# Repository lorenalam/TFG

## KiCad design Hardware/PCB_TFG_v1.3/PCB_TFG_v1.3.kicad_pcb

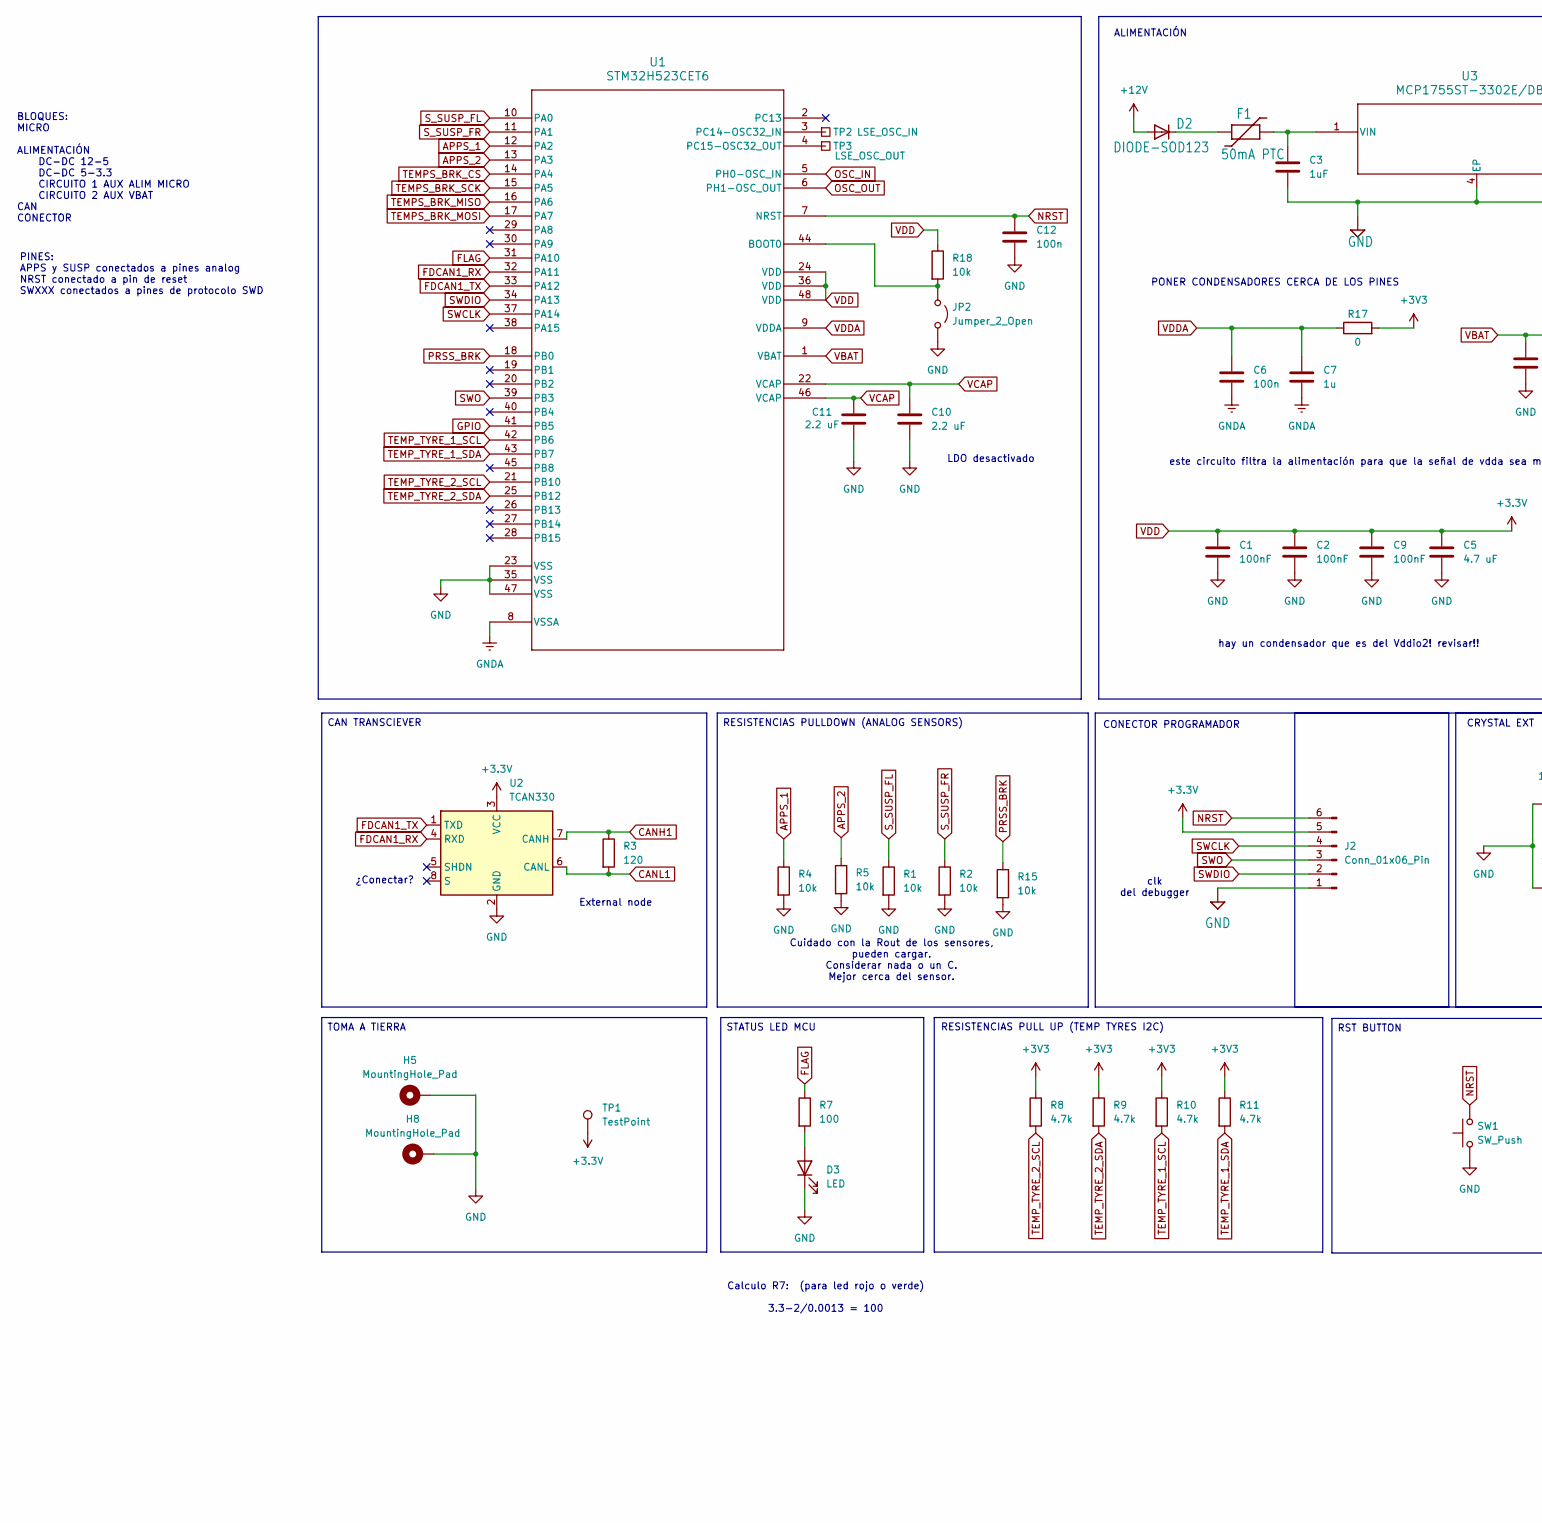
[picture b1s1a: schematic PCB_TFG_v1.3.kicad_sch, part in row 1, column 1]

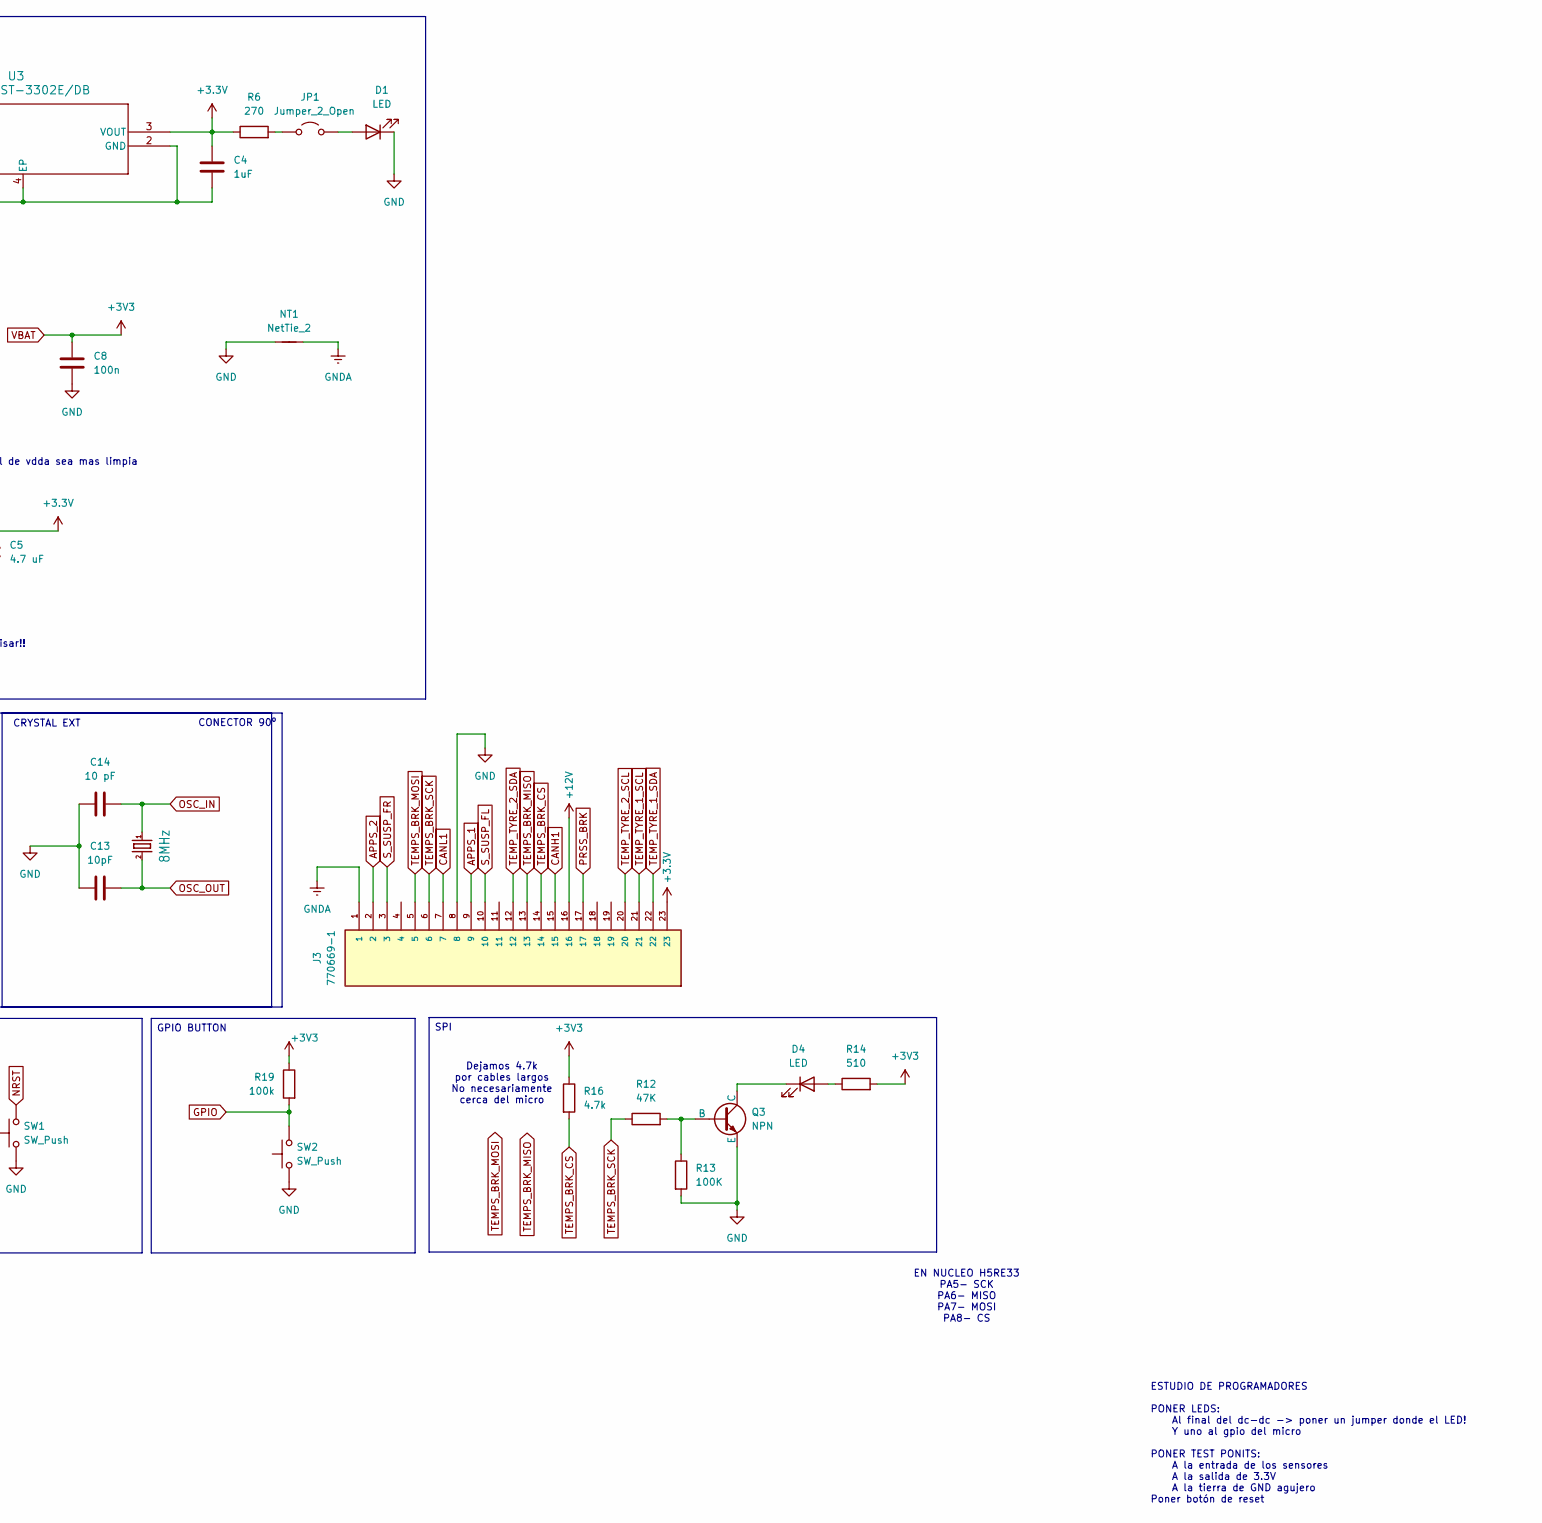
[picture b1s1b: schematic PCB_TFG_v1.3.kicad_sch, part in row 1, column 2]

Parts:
C1, C2, C9: 100nF; C_0805_2012Metric_Pad1.18x1.45mm_HandSolder
C3, C4: 1uF; C_0805_2012Metric_Pad1.18x1.45mm_HandSolder
C5: 4.7 uF; C_0805_2012Metric_Pad1.18x1.45mm_HandSolder
C6, C8, C12: 100n; C_0805_2012Metric_Pad1.18x1.45mm_HandSolder
C7: 1u; C_0805_2012Metric_Pad1.18x1.45mm_HandSolder
C10, C11: 2.2 uF; C_0805_2012Metric_Pad1.18x1.45mm_HandSolder
C13: 10pF; C_0805_2012Metric_Pad1.18x1.45mm_HandSolder
C14: 10 pF; C_0805_2012Metric_Pad1.18x1.45mm_HandSolder
D1, D3, D4: LED; LED_0805_2012Metric_Pad1.15x1.40mm_HandSolder
D2: DIODE-SOD123; SOD123
F1: 50mA PTC; 1206
H5, H8: MountingHole_Pad; MountingHole_3.2mm_M3_ISO14580_Pad_TopBottom
J2: Conn_01x06_Pin; PinHeader_2x03_P2.54mm_Vertical
J3: 770669-1; TE_770669-1; PARTREV K11
JP1: Jumper_2_Open; SolderJumper-2_P1.3mm_Open_RoundedPad1.0x1.5mm
JP2: Jumper_2_Open; PinHeader_1x02_P2.54mm_Vertical
NT1: NetTie_2; NetTie-2_SMD_Pad0.5mm
Q1: 8MHz; CTS406
Q3: NPN; TSOT-23
R1, R2, R4, R5, R15, R18: 10k; R_0805_2012Metric_Pad1.20x1.40mm_HandSolder
R3: 120; R_0805_2012Metric_Pad1.20x1.40mm_HandSolder
R6: 270; R_0805_2012Metric_Pad1.20x1.40mm_HandSolder
R7: 100; R_0805_2012Metric_Pad1.20x1.40mm_HandSolder
R8, R9, R10, R11, R16: 4.7k; R_0805_2012Metric_Pad1.20x1.40mm_HandSolder
R12: 47K; R_0805_2012Metric_Pad1.20x1.40mm_HandSolder
R13: 100K; R_0805_2012Metric_Pad1.20x1.40mm_HandSolder
R14: 510; R_0805_2012Metric_Pad1.20x1.40mm_HandSolder
R17: 0; R_0805_2012Metric_Pad1.20x1.40mm_HandSolder
R19: 100k; R_0805_2012Metric_Pad1.20x1.40mm_HandSolder
SW1, SW2: SW_Push; SW_SPST_B3U-1000P-B
TP1: TestPoint; Pin_D1.0mm_L10.0mm
TP2: LSE_OSC_IN; TestPoint_Pad_1.0x1.0mm
TP3: LSE_OSC_OUT; TestPoint_Pad_1.0x1.0mm
U1: STM32H523CET6; LQFP48_STM
U2: TCAN330; SOIC-8_3.9x4.9mm_P1.27mm
U3: MCP1755ST-3302E/DB; SOT-223_3MC_MCH

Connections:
+12V: D2.A, J3.16
APPS_1: J3.9, R4.1, U1.12 (PA2)
APPS_2: J3.2, R5.1, U1.13 (PA3)
CANH1: J3.15, R3.1, U2.7 (CANH)
CANL1: J3.7, R3.2, U2.6 (CANL)
FDCAN1_RX: U1.32 (PA11), U2.4 (RXD)
FDCAN1_TX: U1.33 (PA12), U2.1 (TXD)
FLAG: R7.1, U1.31 (PA10)
GND: C1.2, C2.2, C3.2, C4.2, C5.2, C8.1, C9.2, C10.2, C11.2, C12.1, C13.1, C14.1, D1.1 (K), D3.1 (K), H5.1 (1_1), H8.1 (1_1), J2.1, J3.8, JP2.2 (B), NT1.1, Q3.3 (E), R1.2, R2.2, R4.2, R5.2, R13.2, R15.2, SW1.1, SW2.1, U1.23 (VSS), U1.35 (VSS), U1.47 (VSS), U2.2 (GND), U3.2 (GND), U3.4 (EP)
GNDA: C6.1, C7.1, J3.1, NT1.2, U1.8 (VSSA)
GPIO: R19.2, SW2.2, U1.41 (PB5)
NRST: C12.2, J2.6, SW1.2, U1.7 (NRST)
unnamed: D1.2 (A), JP1.2 (B)
unnamed: D2.C, F1.P$1
unnamed: D3.2 (A), R7.2
unnamed: D4.2 (A), R14.1
unnamed: D4.1 (K), Q3.1 (C)
unnamed: JP1.1 (A), R6.2
unnamed: JP2.1 (A), R18.2, U1.44 (BOOT0)
unnamed: Q3.2 (B), R12.2, R13.1
unnamed: TP2.1 (1_1), U1.3 (PC14-OSC32_IN)
unnamed: TP3.1 (1_1), U1.4 (PC15-OSC32_OUT)
unnamed: C3.1, F1.P$2, U3.1 (VIN)
OSC_IN: C14.2, Q1.1, U1.5 (PH0-OSC_IN)
OSC_OUT: C13.2, Q1.3 (2), U1.6 (PH1-OSC_OUT)
PRSS_BRK: J3.17, R15.1, U1.18 (PB0)
SWCLK: J2.4, U1.37 (PA14)
SWDIO: J2.2, U1.34 (PA13)
SWO: J2.3, U1.39 (PB3)
S_SUSP_FL: J3.10, R1.1, U1.10 (PA0)
S_SUSP_FR: J3.3, R2.1, U1.11 (PA1)
TEMPS_BRK_CS: J3.14, R16.2, U1.14 (PA4)
TEMPS_BRK_MISO: J3.13, U1.16 (PA6)
TEMPS_BRK_MOSI: J3.5, U1.17 (PA7)
TEMPS_BRK_SCK: J3.6, R12.1, U1.15 (PA5)
TEMP_TYRE_1_SCL: J3.21, R10.2, U1.42 (PB6)
TEMP_TYRE_1_SDA: J3.22, R11.2, U1.43 (PB7)
TEMP_TYRE_2_SCL: J3.20, R8.2, U1.21 (PB10)
TEMP_TYRE_2_SDA: J3.12, R9.2, U1.25 (PB12)
VBAT: C8.2, R8.1, R9.1, R10.1, R11.1, R14.2, R16.1, R17.2, R19.1, U1.1 (VBAT)
VCAP: C10.1, C11.1, U1.22 (VCAP), U1.46 (VCAP)
VDD: C1.1, C2.1, C4.1, C5.1, C9.1, J2.5, J3.23, R6.1, R18.1, TP1.1 (1_1), U1.24 (VDD), U1.36 (VDD), U1.48 (VDD), U2.3 (VCC), U3.3 (VOUT)
VDDA: C6.2, C7.2, R17.1, U1.9 (VDDA)

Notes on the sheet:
PONER CONDENSADORES CERCA DE LOS PINES
ESTUDIO DE PROGRAMADORES PONER LEDS: Al final del dc-dc -> poner un jumper donde el LED! Y uno al gpio del micro PONER TEST PONITS: A la entrada de los sensores A la salida de 3.3V A la tierra de GND agujero Poner botón de reset
EN NUCLEO H5RE33 PA5- SCK PA6- MISO PA7- MOSI PA8- CS
BLOQUES: MICRO ALIMENTACIÓN DC-DC 12-5 DC-DC 5-3.3 CIRCUITO 1 AUX ALIM MICRO CIRCUITO 2 AUX VBAT CAN CONECTOR
CONECTOR PROGRAMADOR
clk del debugger
Cuidado con la Rout de los sensores, pueden cargar. Considerar nada o un C. Mejor cerca del sensor.
RESISTENCIAS PULL UP (TEMP TYRES I2C)
Calculo R7: (para led rojo o verde) 3.3-2/0.0013 = 100
Dejamos 4.7k por cables largos No necesariamente cerca del micro
External node
LDO desactivado
este circuito filtra la alimentación para que la señal de vdda sea mas limpia
¿Conectar?
PINES: APPS y SUSP conectados a pines analog NRST conectado a pin de reset SWXXX conectados a pines de protocolo SWD
hay un condensador que es del Vddio2! revisar!!
ALIMENTACIÓN
CRYSTAL EXT
TOMA A TIERRA
RESISTENCIAS PULLDOWN (ANALOG SENSORS)
GPIO BUTTON
CONECTOR 90º
SPI
CAN TRANSCIEVER
STATUS LED MCU
RST BUTTON

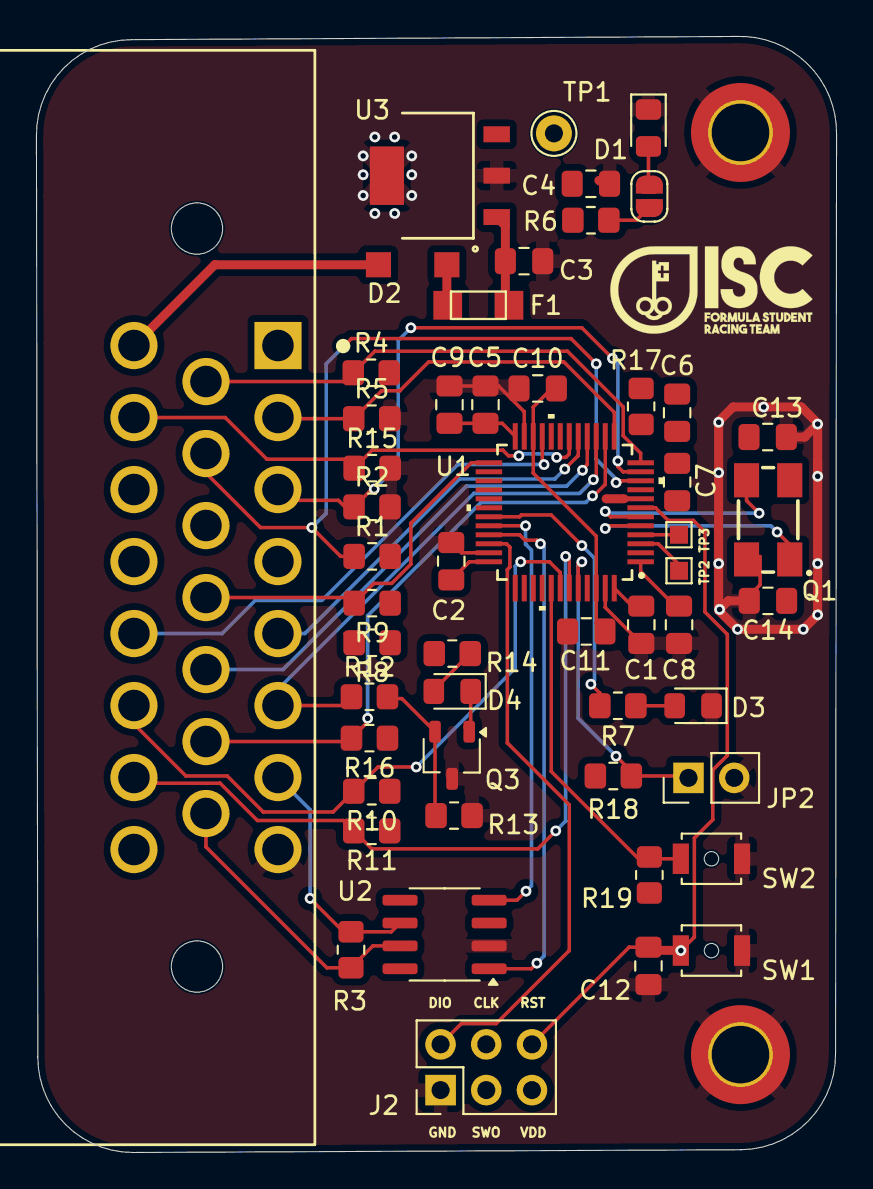
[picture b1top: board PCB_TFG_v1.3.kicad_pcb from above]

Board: 4 copper layers, 44.4 x 62.0 mm, 55 parts (0 on the bottom side), 43 nets.

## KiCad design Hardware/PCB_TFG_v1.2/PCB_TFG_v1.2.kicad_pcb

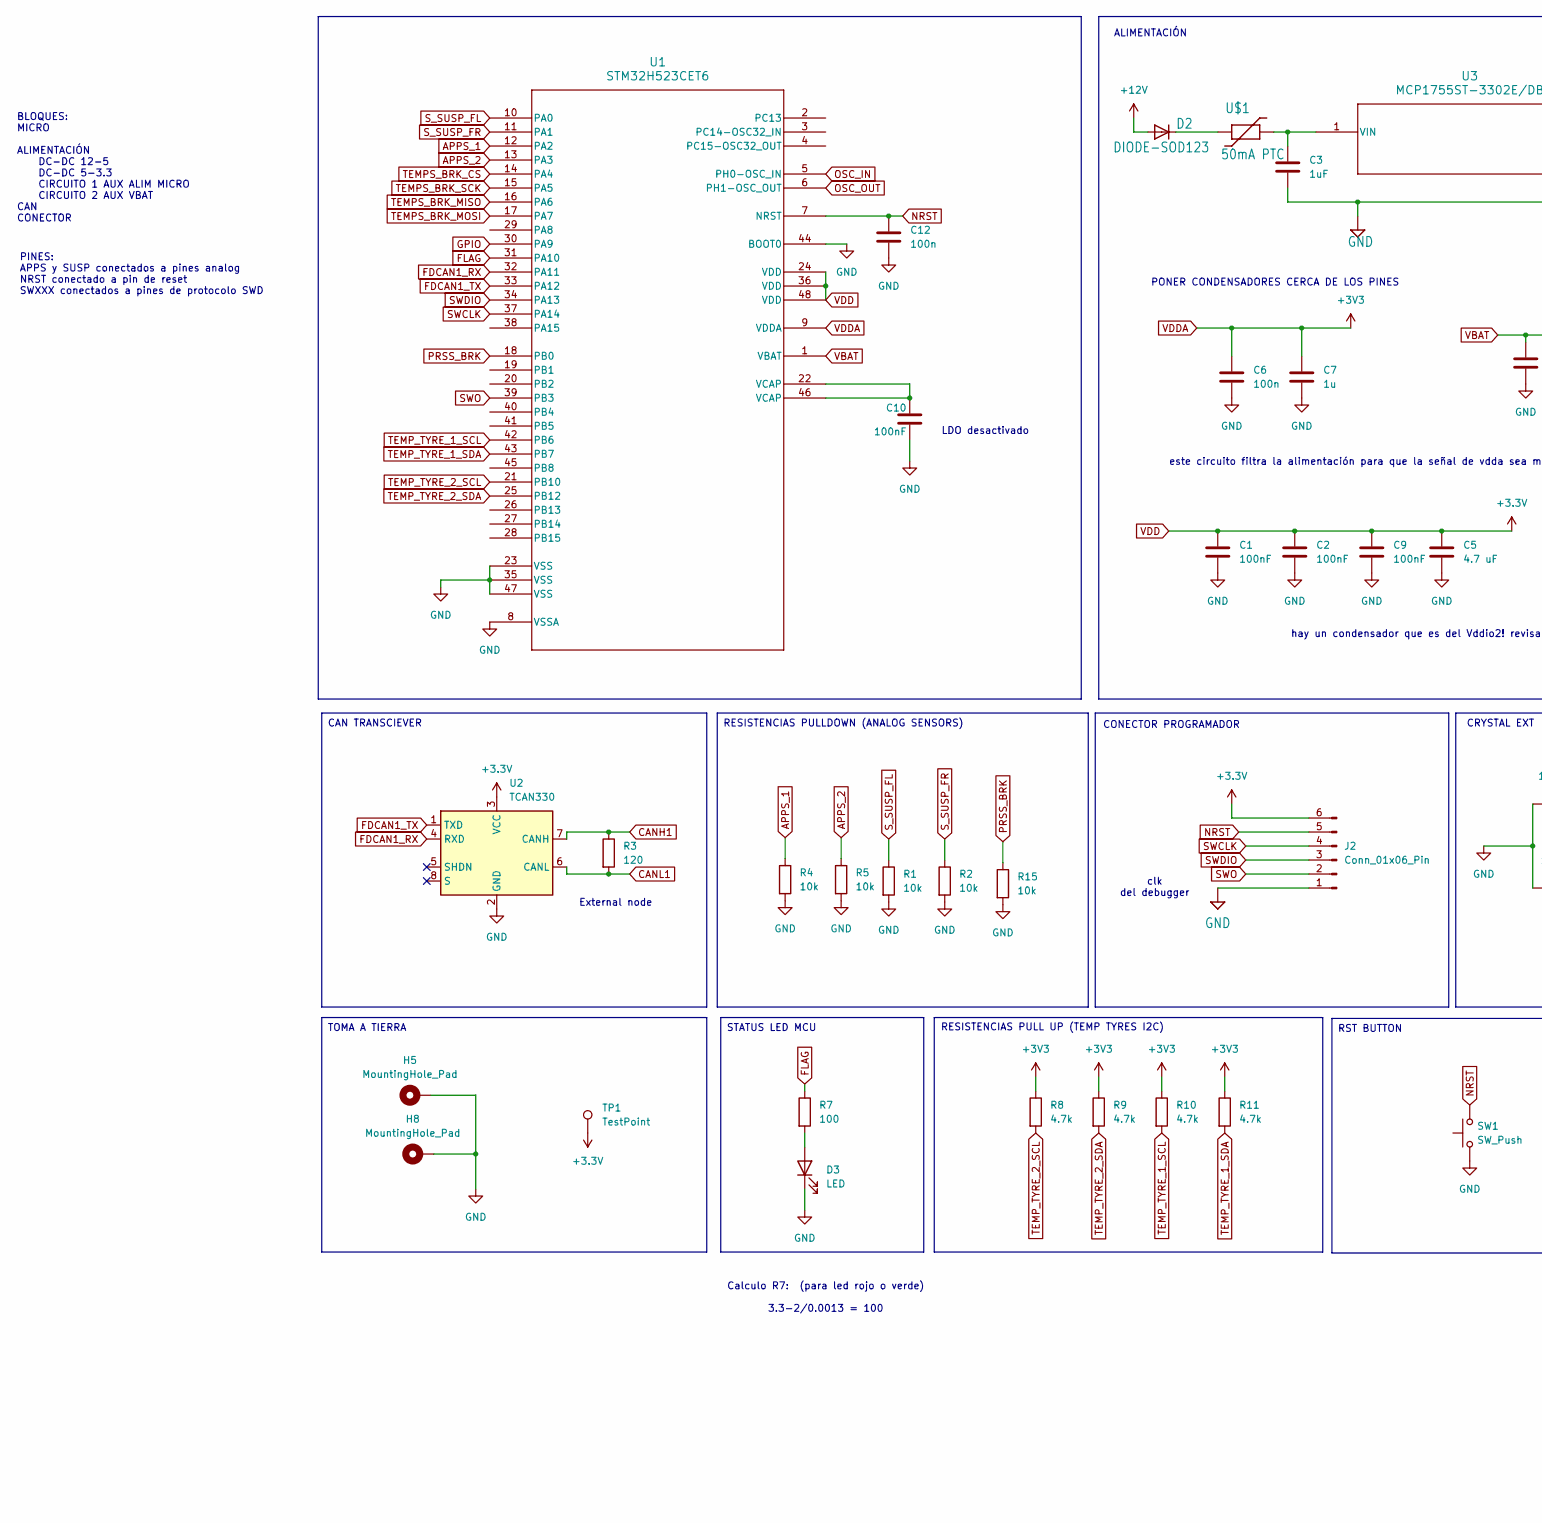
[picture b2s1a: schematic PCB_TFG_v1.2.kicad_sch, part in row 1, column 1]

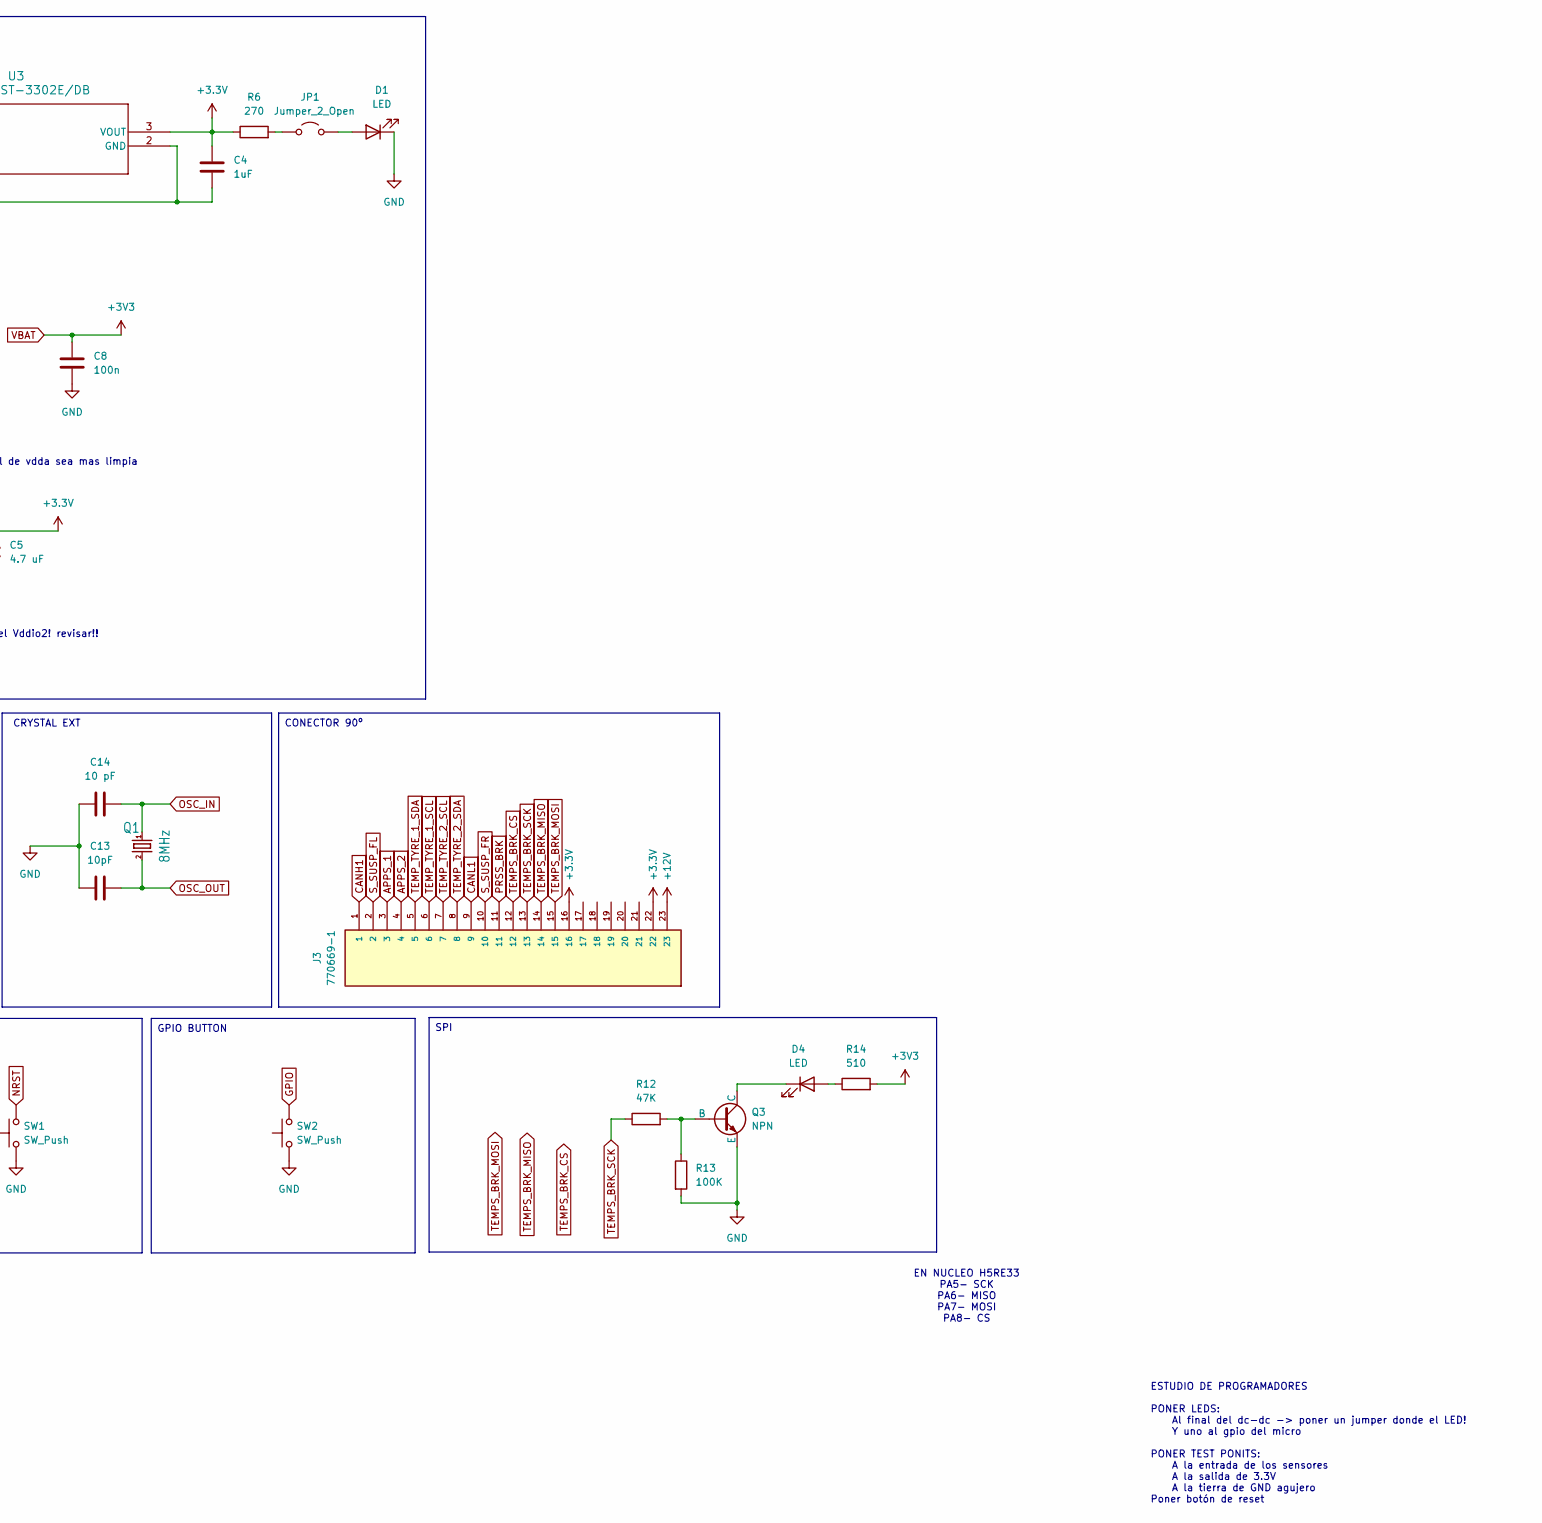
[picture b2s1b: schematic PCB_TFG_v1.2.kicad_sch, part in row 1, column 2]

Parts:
C1, C2, C9, C10: 100nF; C_0805_2012Metric_Pad1.18x1.45mm_HandSolder
C3, C4: 1uF; C_0805_2012Metric_Pad1.18x1.45mm_HandSolder
C5: 4.7 uF; C_0805_2012Metric_Pad1.18x1.45mm_HandSolder
C6, C8: 100n; C_0805_2012Metric_Pad1.18x1.45mm_HandSolder
C7: 1u; C_0805_2012Metric_Pad1.18x1.45mm_HandSolder
C12: 100n; C_0603_1608Metric_Pad1.08x0.95mm_HandSolder
C13: 10pF; C_0805_2012Metric_Pad1.18x1.45mm_HandSolder
C14: 10 pF; C_0805_2012Metric_Pad1.18x1.45mm_HandSolder
D1, D3, D4: LED; LED_0805_2012Metric_Pad1.15x1.40mm_HandSolder
D2: DIODE-SOD123; SOD123
H5, H8: MountingHole_Pad; MountingHole_3.2mm_M3_ISO14580_Pad_TopBottom
J2: Conn_01x06_Pin; PinHeader_2x03_P2.54mm_Vertical
J3: 770669-1; TE_770669-1; PARTREV K11
JP1: Jumper_2_Open; SolderJumper-2_P1.3mm_Open_RoundedPad1.0x1.5mm
Q1: 8MHz; CTS406
Q3: NPN; TSOT-23
R1, R2, R4, R5, R15: 10k; R_0805_2012Metric_Pad1.20x1.40mm_HandSolder
R3: 120; R_0805_2012Metric_Pad1.20x1.40mm_HandSolder
R6: 270; R_0805_2012Metric_Pad1.20x1.40mm_HandSolder
R7: 100; R_0805_2012Metric_Pad1.20x1.40mm_HandSolder
R8, R9, R10, R11: 4.7k; R_0805_2012Metric_Pad1.20x1.40mm_HandSolder
R12: 47K; R_0805_2012Metric_Pad1.20x1.40mm_HandSolder
R13: 100K; R_0805_2012Metric_Pad1.20x1.40mm_HandSolder
R14: 510; R_0805_2012Metric_Pad1.20x1.40mm_HandSolder
SW1, SW2: SW_Push; SW_PUSH_6mm_H4.3mm
TP1: TestPoint; Pin_D1.0mm_L10.0mm
U1: STM32H523CET6; LQFP48_STM
U2: TCAN330; SOIC-8_3.9x4.9mm_P1.27mm
U3: MCP1755ST-3302E/DB; SOT-223_3MC_MCH
U$1: 50mA PTC; 1206

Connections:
+12V: D2.A, J3.23
APPS_1: J3.3, R4.1, U1.12 (PA2)
APPS_2: J3.4, R5.1, U1.13 (PA3)
CANH1: J3.1, R3.1, U2.7 (CANH)
CANL1: J3.9, R3.2, U2.6 (CANL)
FDCAN1_RX: U1.32 (PA11), U2.4 (RXD)
FDCAN1_TX: U1.33 (PA12), U2.1 (TXD)
FLAG: R7.1, U1.31 (PA10)
GND: C1.2, C2.2, C3.2, C4.2, C5.2, C6.1, C7.1, C8.1, C9.2, C10.2, C12.1, C13.1, C14.1, D1.1 (K), D3.1 (K), H5.1, H8.1, J2.1, Q3.3 (E), R1.2, R2.2, R4.2, R5.2, R13.2, R15.2, SW1.1, SW2.1, U1.8 (VSSA), U1.23 (VSS), U1.35 (VSS), U1.44 (BOOT0), U1.47 (VSS), U2.2 (GND), U3.2 (GND)
GPIO: SW2.2, U1.30 (PA9)
NRST: C12.2, J2.5, SW1.2, U1.7 (NRST)
unnamed: C10.1, U1.22 (VCAP), U1.46 (VCAP)
unnamed: D1.2 (A), JP1.2 (B)
unnamed: D2.C, U$1.P$1
unnamed: D3.2 (A), R7.2
unnamed: D4.2 (A), R14.1
unnamed: D4.1 (K), Q3.1 (C)
unnamed: JP1.1 (A), R6.2
unnamed: Q3.2 (B), R12.2, R13.1
unnamed: C3.1, U3.1 (VIN), U$1.P$2
OSC_IN: C14.2, Q1.1, U1.5 (PH0-OSC_IN)
OSC_OUT: C13.2, Q1.3 (2), U1.6 (PH1-OSC_OUT)
PRSS_BRK: J3.11, R15.1, U1.18 (PB0)
SWCLK: J2.4, U1.37 (PA14)
SWDIO: J2.3, U1.34 (PA13)
SWO: J2.2, U1.39 (PB3)
S_SUSP_FL: J3.2, R1.1, U1.10 (PA0)
S_SUSP_FR: J3.10, R2.1, U1.11 (PA1)
TEMPS_BRK_CS: J3.12, U1.14 (PA4)
TEMPS_BRK_MISO: J3.14, U1.16 (PA6)
TEMPS_BRK_MOSI: J3.15, U1.17 (PA7)
TEMPS_BRK_SCK: J3.13, R12.1, U1.15 (PA5)
TEMP_TYRE_1_SCL: J3.6, R10.2, U1.42 (PB6)
TEMP_TYRE_1_SDA: J3.5, R11.2, U1.43 (PB7)
TEMP_TYRE_2_SCL: J3.7, R8.2, U1.21 (PB10)
TEMP_TYRE_2_SDA: J3.8, R9.2, U1.25 (PB12)
VBAT: C6.2, C7.2, C8.2, R8.1, R9.1, R10.1, R11.1, R14.2, U1.1 (VBAT), U1.9 (VDDA)
VDD: C1.1, C2.1, C4.1, C5.1, C9.1, J2.6, J3.16, J3.22, R6.1, TP1.1, U1.24 (VDD), U1.36 (VDD), U1.48 (VDD), U2.3 (VCC), U3.3 (VOUT)

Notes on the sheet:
TOMA A TIERRA
RESISTENCIAS PULLDOWN (ANALOG SENSORS)
GPIO BUTTON
CONECTOR 90º
SPI
CAN TRANSCIEVER
STATUS LED MCU
RST BUTTON
PONER CONDENSADORES CERCA DE LOS PINES
ESTUDIO DE PROGRAMADORES PONER LEDS: Al final del dc-dc -> poner un jumper donde el LED! Y uno al gpio del micro PONER TEST PONITS: A la entrada de los sensores A la salida de 3.3V A la tierra de GND agujero Poner botón de reset
EN NUCLEO H5RE33 PA5- SCK PA6- MISO PA7- MOSI PA8- CS
BLOQUES: MICRO ALIMENTACIÓN DC-DC 12-5 DC-DC 5-3.3 CIRCUITO 1 AUX ALIM MICRO CIRCUITO 2 AUX VBAT CAN CONECTOR
CONECTOR PROGRAMADOR
clk del debugger
RESISTENCIAS PULL UP (TEMP TYRES I2C)
Calculo R7: (para led rojo o verde) 3.3-2/0.0013 = 100
External node
LDO desactivado
este circuito filtra la alimentación para que la señal de vdda sea mas limpia
PINES: APPS y SUSP conectados a pines analog NRST conectado a pin de reset SWXXX conectados a pines de protocolo SWD
hay un condensador que es del Vddio2! revisar!!
ALIMENTACIÓN
CRYSTAL EXT

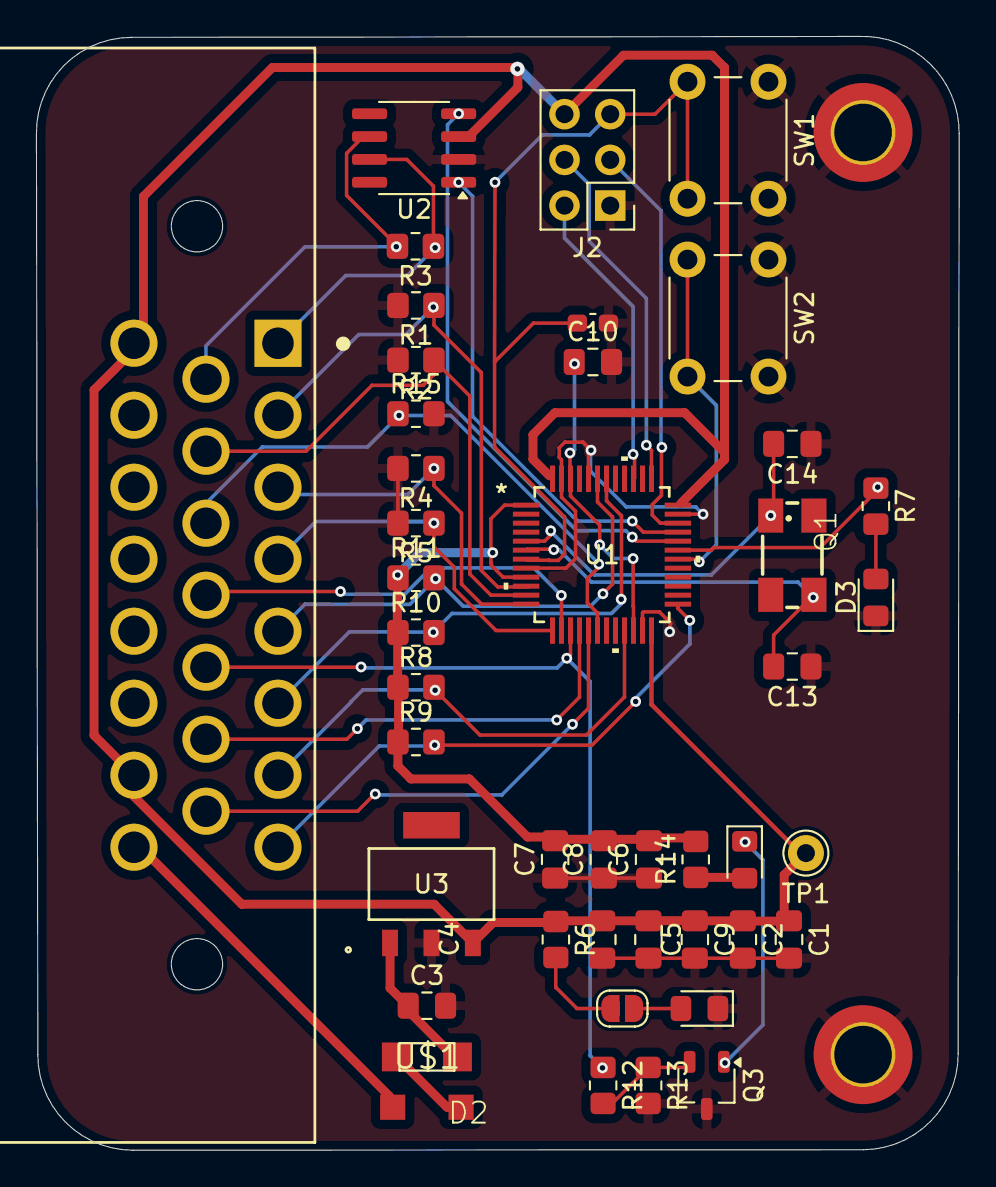
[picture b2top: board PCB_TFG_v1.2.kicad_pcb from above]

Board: 2 copper layers, 51.3 x 61.9 mm, 46 parts (0 on the bottom side), 38 nets.

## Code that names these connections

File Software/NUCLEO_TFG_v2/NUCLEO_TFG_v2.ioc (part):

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Mcu.Name=STM32H533RETx
Mcu.Package=LQFP64
Mcu.UserName=STM32H533RETx
PA0.GPIOParameters=GPIO_Label
PA0.GPIO_Label=APPS_1
PA0.Signal=ADCx_INP0
PA1.GPIOParameters=GPIO_Label
PA1.GPIO_Label=APPS_2
PA1.Signal=ADCx_INP1
PA11.Mode=FDCAN_Activate
PA11.Signal=FDCAN1_RX
PA12.Mode=FDCAN_Activate
PA12.Signal=FDCAN1_TX
PA13(JTMS/SWDIO).GPIOParameters=GPIO_Label
PA13(JTMS/SWDIO).GPIO_Label=SWDIO
PA13(JTMS/SWDIO).Signal=DEBUG_JTMS-SWDIO
PA14(JTCK/SWCLK).GPIOParameters=GPIO_Label
PA14(JTCK/SWCLK).GPIO_Label=SWCLK
PA14(JTCK/SWCLK).Signal=DEBUG_JTCK-SWCLK
PA15(JTDI).GPIOParameters=GPIO_Label
PA15(JTDI).GPIO_Label=JTDI
PA15(JTDI).Signal=DEBUG_JTDI
PA2.Signal=USART2_TX
PA3.Signal=USART2_RX
PA6.GPIOParameters=GPIO_Label
PA6.GPIO_Label=SUSP_FL
PA6.Signal=ADCx_INP3
PA8.GPIOParameters=GPIO_Label
PA8.GPIO_Label=SPI2_TEMP_BRK
PA8.Signal=GPIO_Output
PB1.GPIOParameters=GPIO_Label
PB1.GPIO_Label=PRSS_BRK
PB1.Signal=ADCx_INP5
PB10.GPIOParameters=GPIO_Label
PB10.GPIO_Label=I2C2_SCL_TEMP_TYRE_2
PB10.Mode=I2C
PB10.Signal=I2C2_SCL
PB12.GPIOParameters=GPIO_Label
PB12.GPIO_Label=I2C2_SDA_TEMP_TYRE_2
PB12.Mode=I2C
PB12.Signal=I2C2_SDA
PB2.GPIOParameters=GPIO_Label
PB2.GPIO_Label=SPI2_SCK_TEMP_BRK
PB2.Mode=Full_Duplex_Master
PB2.Signal=SPI2_SCK
PB3(JTDO/TRACESWO).GPIOParameters=GPIO_Label
PB3(JTDO/TRACESWO).GPIO_Label=SWO
PB3(JTDO/TRACESWO).Signal=DEBUG_JTDO-SWO
PB6.GPIOParameters=GPIO_Label
PB6.GPIO_Label=I2C1_SCL_TEMP_TYRE_1
PB6.Mode=I2C
PB6.Signal=I2C1_SCL
PB7.GPIOParameters=GPIO_Label
PB7.GPIO_Label=I2C1_SDA_TEMP_TYRE_1
PB7.Mode=I2C
PB7.Signal=I2C1_SDA
PC1.GPIOParameters=GPIO_Label
PC1.GPIO_Label=SPI2_MOSI_TEMP_BRK
PC1.Mode=Full_Duplex_Master
PC1.Signal=SPI2_MOSI
PC2.GPIOParameters=GPIO_Label
PC2.GPIO_Label=SPI2_MISO_TEMP_BRK
PC2.Mode=Full_Duplex_Master
PC2.Signal=SPI2_MISO
PC4.GPIOParameters=GPIO_Label
PC4.GPIO_Label=SUSP_FR
PC4.Signal=ADCx_INP4
RCC.HSE_VALUE=25000000
RCC.SYSCLKFreq_VALUE=32000000
board=NUCLEO-H533RE
boardIOC=true

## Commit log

2026-01-19 1st upload
    Archivos -prueba canfd -prueba sensores
2026-01-19 Extra docs
2026-01-19 Docs
2026-02-17 v1.2 adc integrado con CANFD
    + prueba aproximada parámetros SPI
2026-02-17 add esquemático nucleoH5
2026-02-25 small change in lectura
2026-04-22 Hardware PCB v1.2
    Versión PCB para posible fabricación
2026-05-07 PCB v1.3
    Cambios:
    Cs de acoplamiento
    Oscilador
    SPI
    Vías alimentación
    Pendiente:
2026-05-25 AÑADIDO PROYECTO KICAD NUCLEO
    - Se añade el proyecto de KiCAD con el PCB y esquema de la tarjeta núcleo, extraída del proyecto de Altium de los recursos de STM
2026-05-25 CREADA LA CARPETA DE DOCUMENTACIÓN PARA PCB
    - Se añaden los documentos para diseño de PCB de STM
    - Se añaden los documentos para cálculo de Heat Sink
2026-05-25 MODIFICACIONES AL PCB
    - Separación de Áreas Analógica y Digital.
    - Creación de dos planos de GND y Vcc en capas intermedias.
    - Recolocación de los C de desacoplo.
2026-05-29 ENRUTADO COMPLETADO
    - Nueva versión del PCB ya enrutado.
    - Modificadas huellas de algunos componentes, principalmente para incluir marca de posición.
2026-06-25 Actualización e integración SW v2
